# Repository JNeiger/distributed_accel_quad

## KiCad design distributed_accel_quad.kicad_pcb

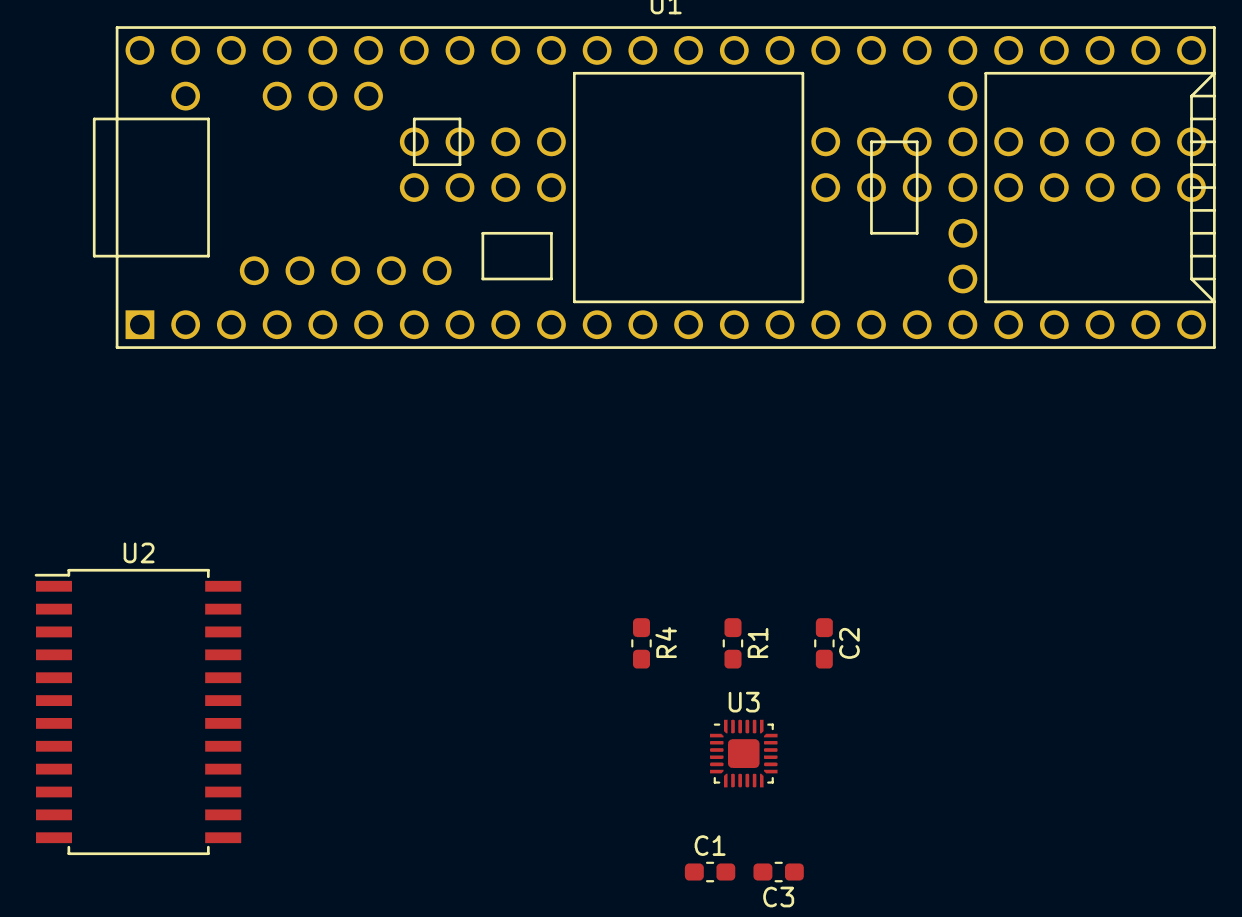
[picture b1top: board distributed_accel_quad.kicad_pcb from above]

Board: 2 copper layers, 8 parts (0 on the bottom side), 10 nets, no tracks yet.

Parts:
C1: 10nF; C_0603_1608Metric_Pad1.05x0.95mm_HandSolder
C2, C3: 0.1uF; C_0603_1608Metric_Pad1.05x0.95mm_HandSolder
R1, R4: 4.7K; R_0603_1608Metric_Pad1.05x0.95mm_HandSolder
U1: Teensy3.6; Teensy35_36
U2: CD74HC4067M; SOIC-24W_7.5x15.4mm_P1.27mm
U3: MPU-9250; QFN-24-1EP_3x3mm_P0.4mm_EP1.75x1.6mm

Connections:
3.3V: C1.1, C2.1, R1.1, R4.1, U1.51, U2.24, U3.1, U3.8, U3.13, U3.22
Earth: C1.2, C2.2, C3.2, U2.12, U2.15, U3.9, U3.18, U3.20
unnamed: C3.1, U3.10
S0: U1.7, U2.10
S1: U1.8, U2.11
S2: U1.9, U2.14
S3: U1.10, U2.13
SCL: R1.2, U1.46, U3.23
SDA: U1.45, U2.1
SDA1: R4.2, U2.9, U3.24

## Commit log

2018-08-02 Removed some resistors that aren't needed
